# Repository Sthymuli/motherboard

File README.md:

\# Sthymuli-motherboard
This repo contains the PCB for the Sthymuli motherboard. Sthymuli is an educative robot aimed at children whith the aim of promoting collaborative learning.

The motherboard is designed arround a doughnut shape with addons that plug in the center. the shape was chosen to encourage equal access to up to four children at a time interracting with the device.

## 3D view

| Top | Bottom |
|---|---|
|  |  |

## Exports

Regenerated automatically by the [export workflow](.github/workflows/export.yml) on every push to `main` that changes the design:

* [Schematic (PDF)](exports/Sthymuli-motherboard_schematic.pdf)
* [Layout (PDF, one page per layer)](exports/Sthymuli-motherboard_layout.pdf)
* [3D model (STEP)](exports/Sthymuli-motherboard.step), with only the parts placed on the board
* [3D render, top](exports/Sthymuli-motherboard_3d_top.png) / [bottom](exports/Sthymuli-motherboard_3d_bottom.png)

To run the same export locally: `scripts/export.sh` (see the comment at the top of the script for the Flatpak KiCad variant).

The cardinal board can be found [here](https://github.com/Sthymuli/cardinalboard).

# Feature
The device contains the following sensors 

===

* # USB-C connector
* # Batterie + BMS
* # ESP32 + STM32
* # Speaker
* # Microphone
* # capacitive buttons (distributed arround the doughnut as discussed last time)
* # IR remote receive
* # 4 IR proximity Sensor
* # Motor Driver (so they can just connect the two wire of the motor and dont need to add a Hbridge on the dauther board
* # RGB LED (there I need to count how many and decide with you what we keep and what we breakout for the daugther board

\# Daugther boards

the following will be available for the daugther board :

* IMU
* color sensor
* 2 DC motor channel
* LEDs
* IR proximity sensor / analog pin that can be used for sensing

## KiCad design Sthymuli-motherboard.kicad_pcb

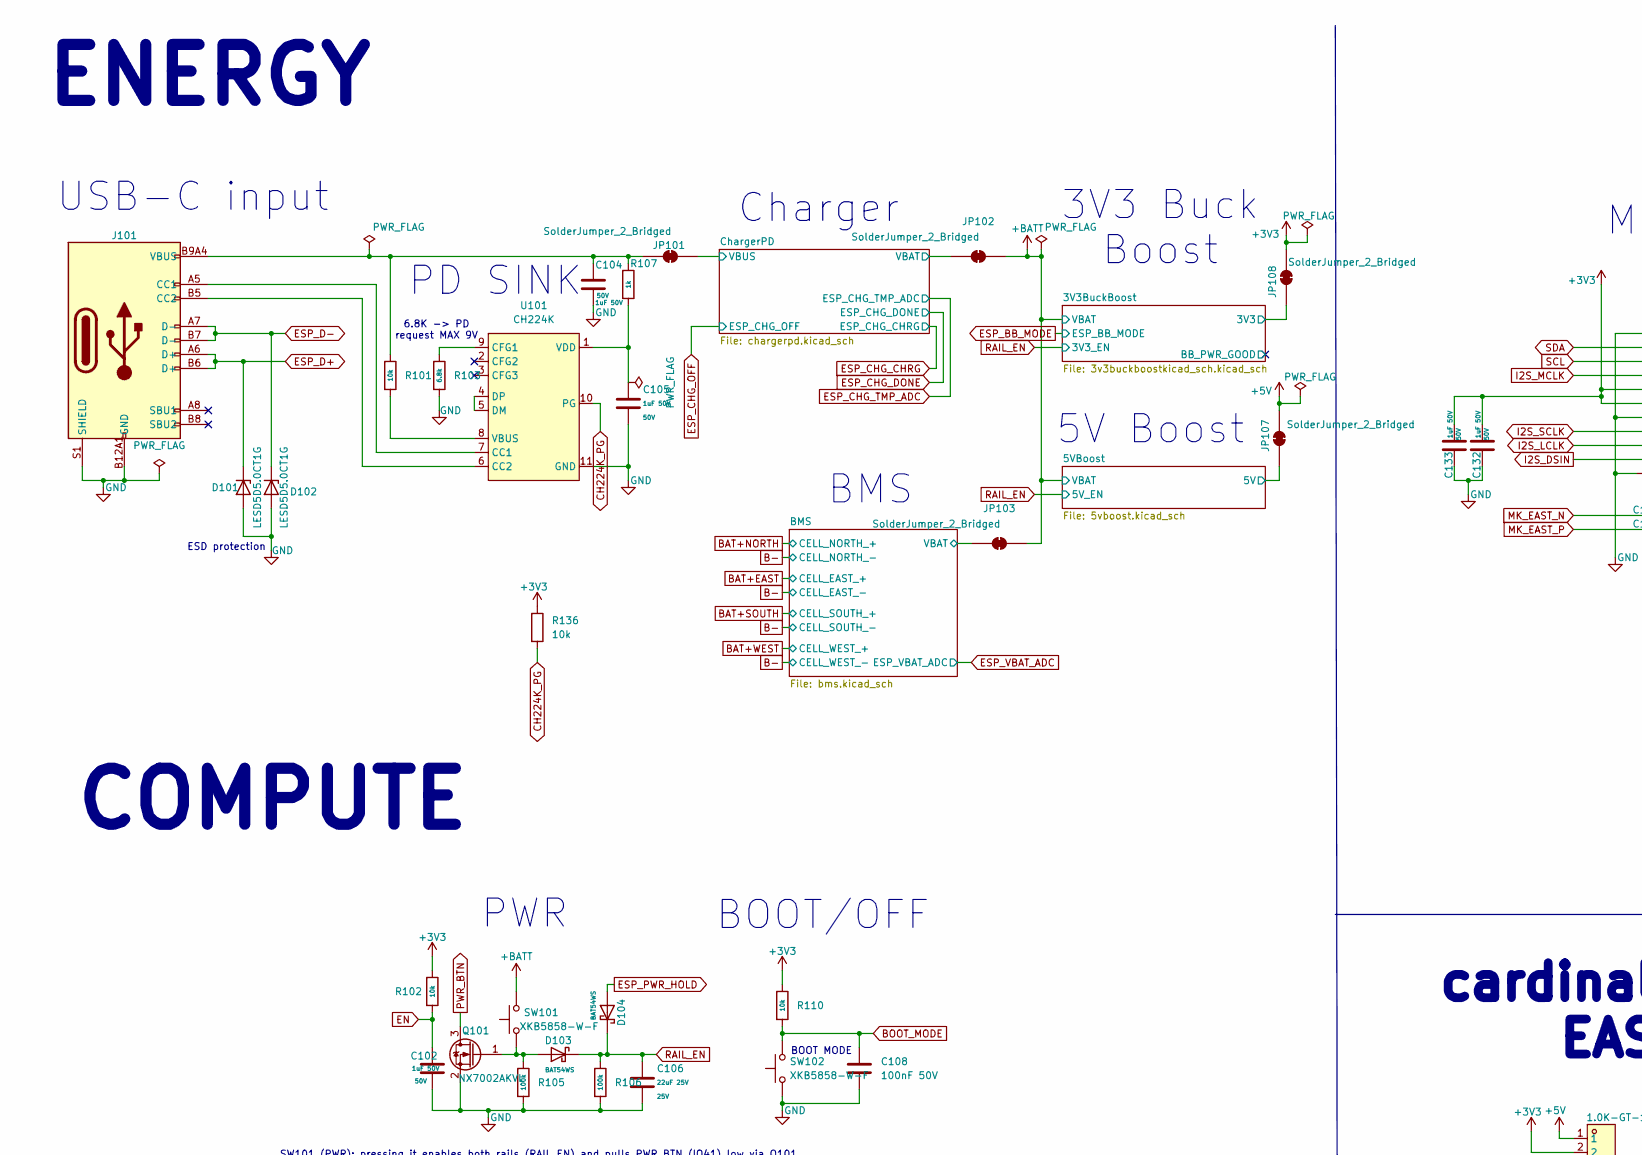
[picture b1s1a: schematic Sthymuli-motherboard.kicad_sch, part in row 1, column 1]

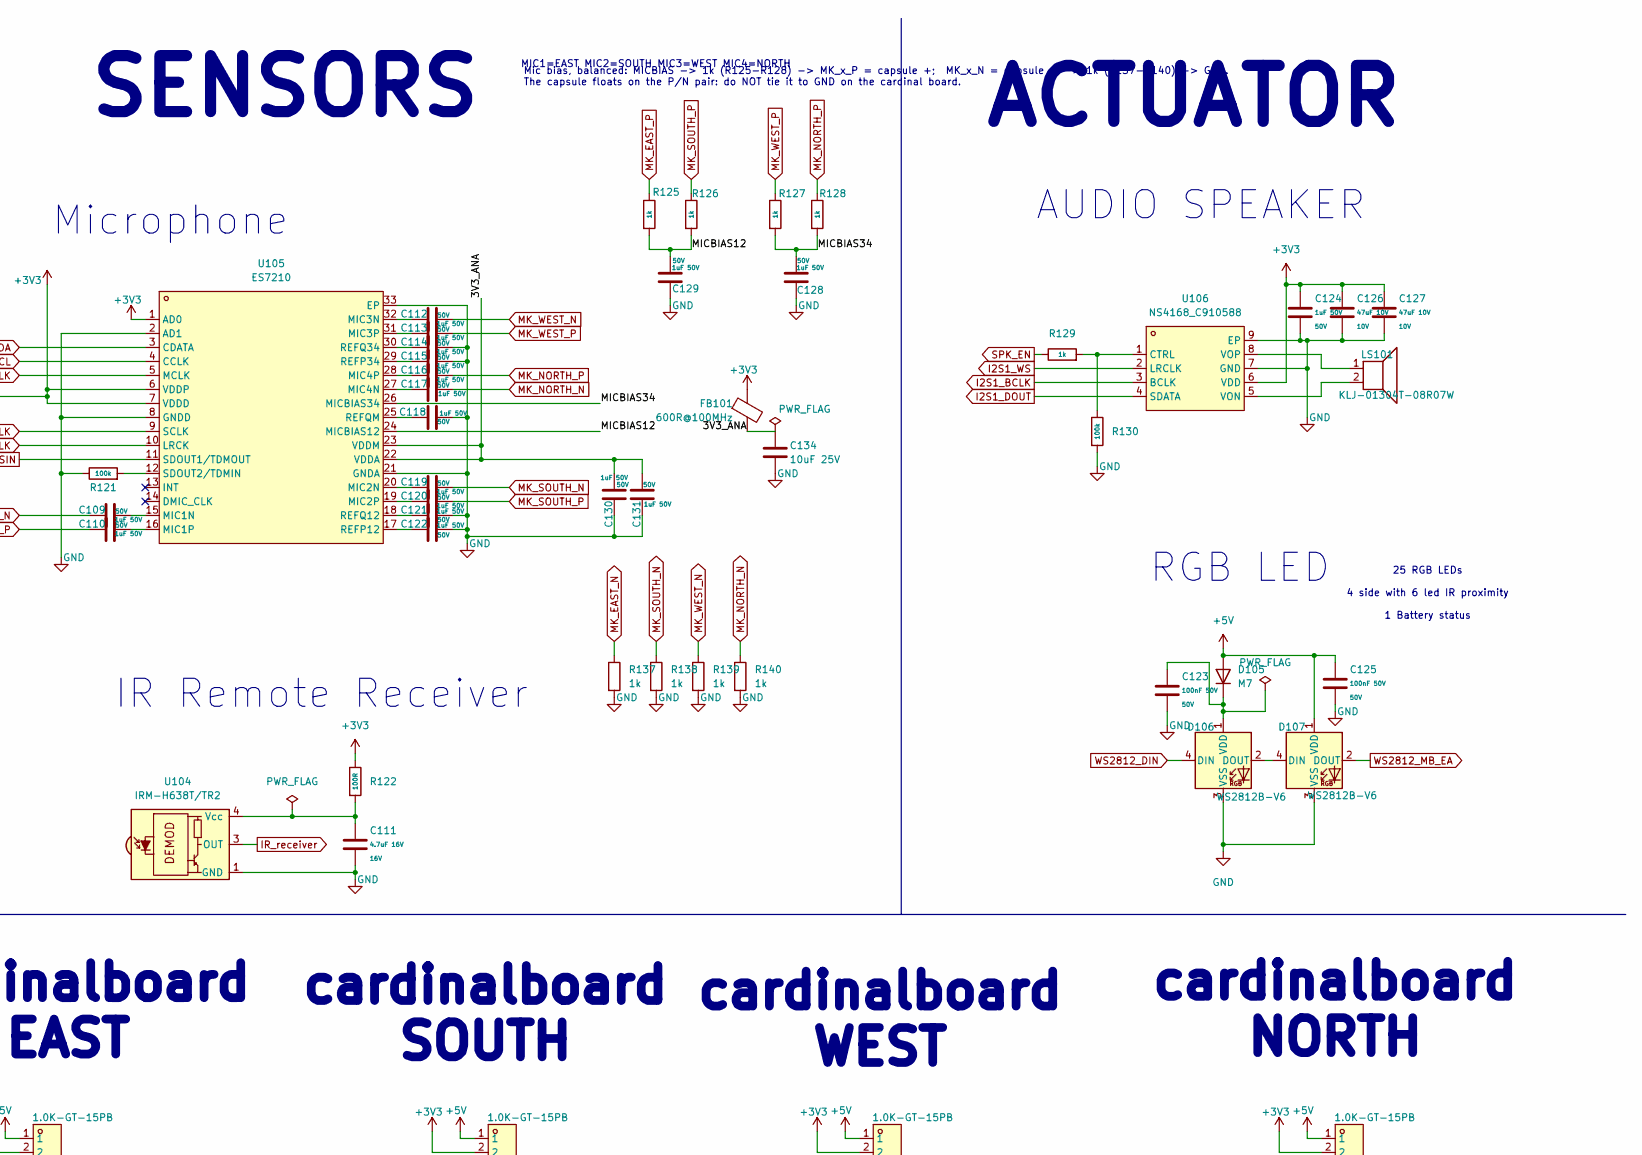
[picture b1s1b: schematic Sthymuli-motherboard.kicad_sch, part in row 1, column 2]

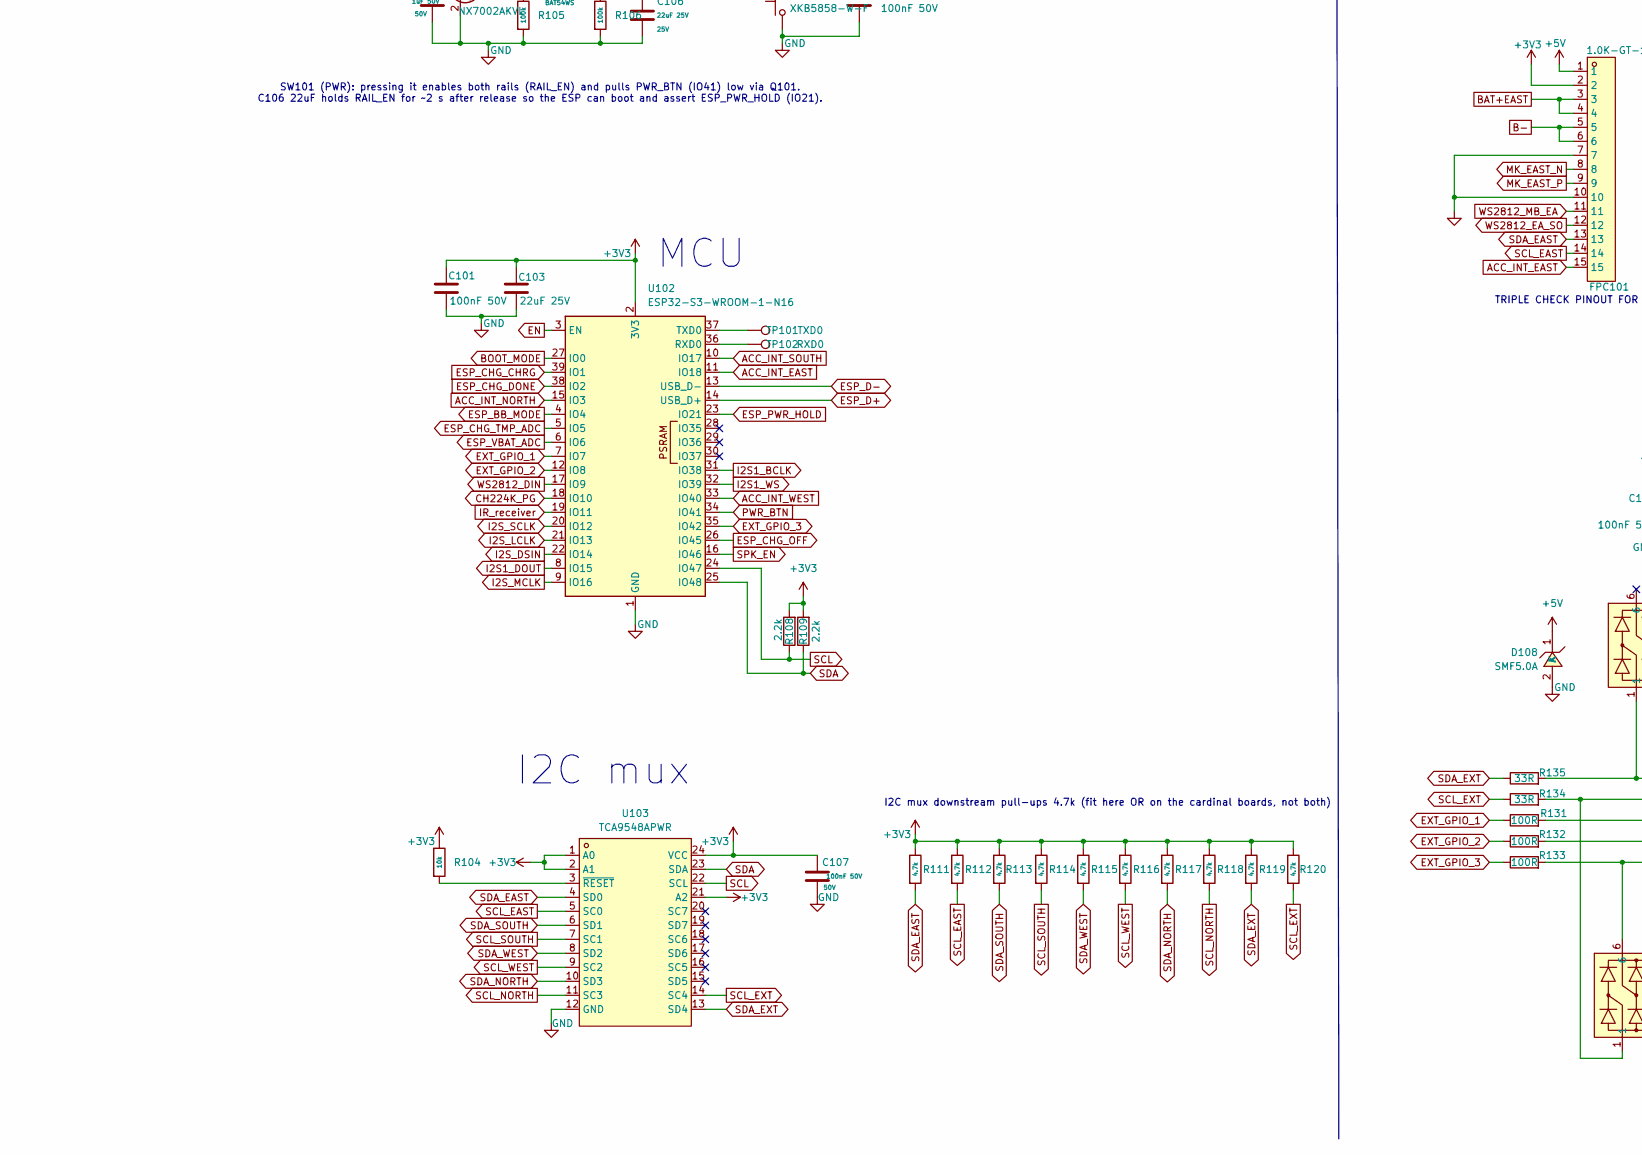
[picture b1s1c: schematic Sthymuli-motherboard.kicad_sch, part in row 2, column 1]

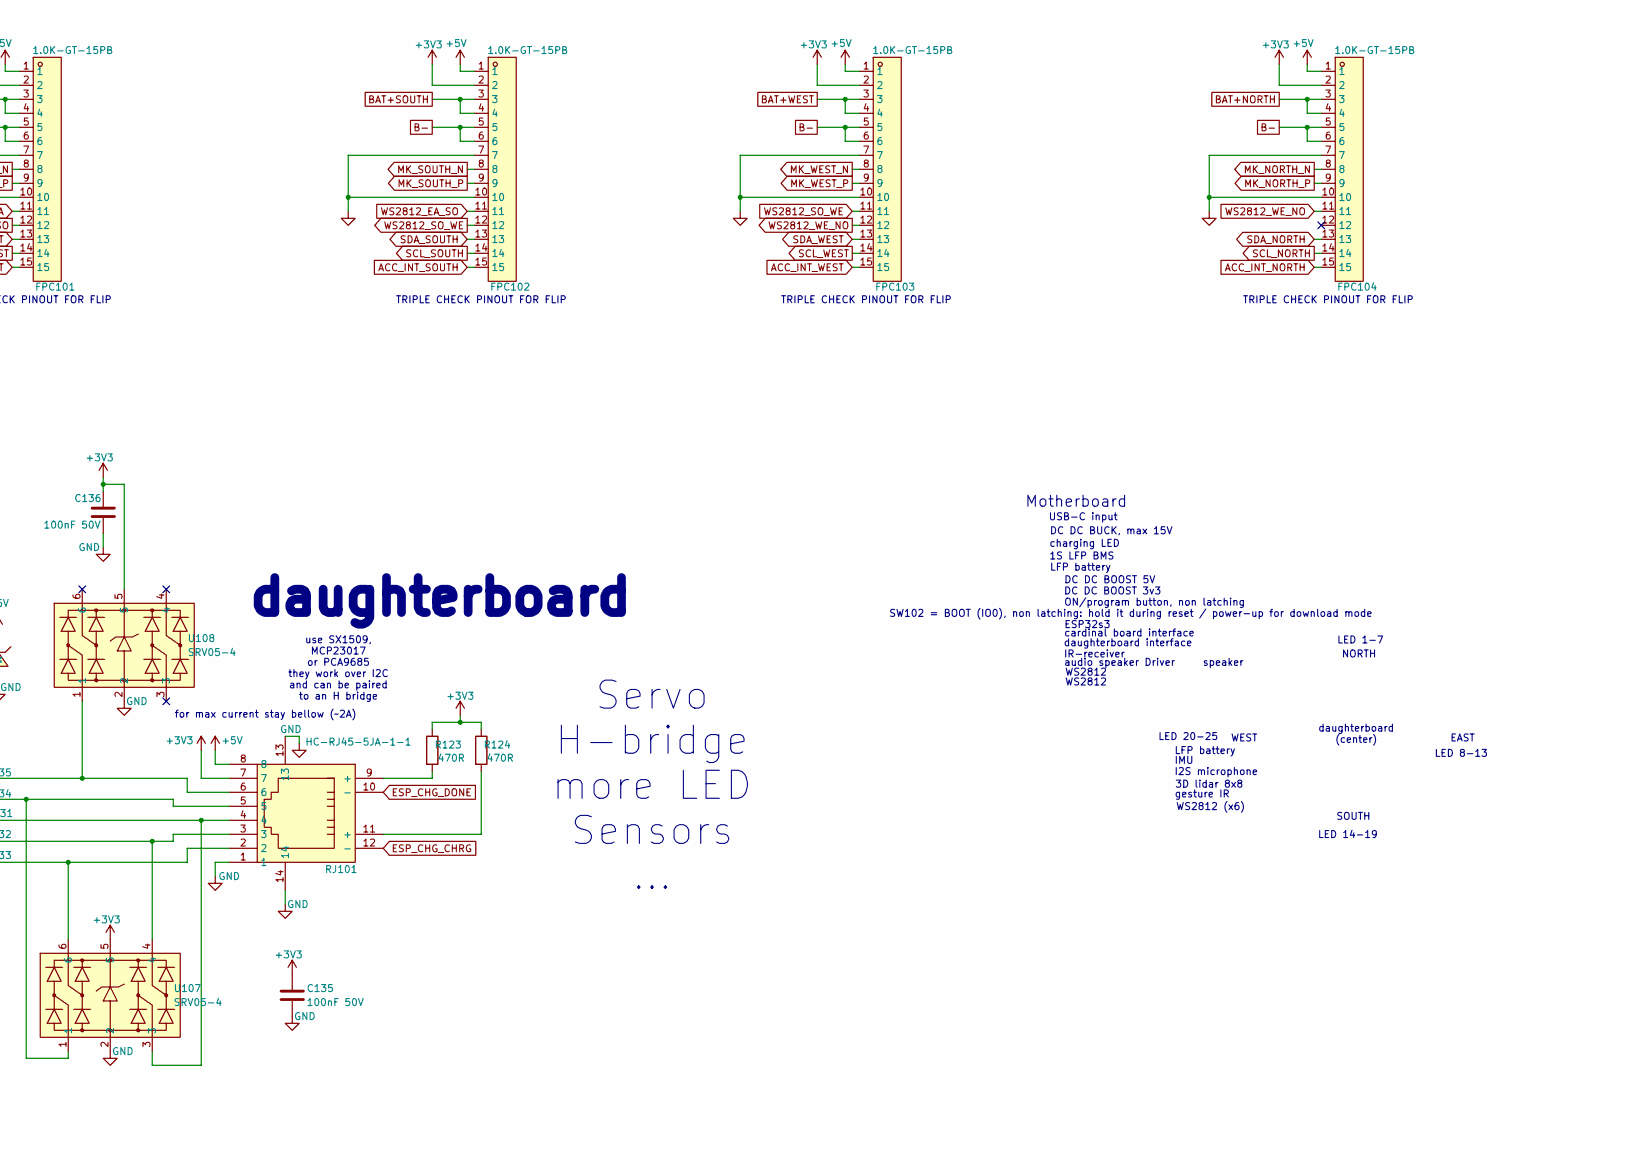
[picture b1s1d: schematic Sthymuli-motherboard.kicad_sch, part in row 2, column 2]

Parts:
C101, C108, C135, C136: 100nF 50V; C_0603_1608Metric; LCSC C14663
C102, C104, C105, C109, C110, C112, C113, C114, C115, C116, C117, C118, C119, C120, C121, C122, C124, C128, C129, C130, C131, C132, C133: 1uF 50V; C_0603_1608Metric; Voltage Rated 50V; Tolerance ±10%; Part CL10A105KB8NNNC; LCSC C15849
C103: 22uF 25V; C_0805_2012Metric; LCSC C45783
C106: 22uF 25V; C_0805_2012Metric; Voltage Rated 25V; Tolerance ±20%; Part CL21A226MAQNNNE; LCSC C45783
C107, C123, C125: 100nF 50V; C_0603_1608Metric; Voltage Rated 50V; Tolerance ±10%; Part CC0603KRX7R9BB104; LCSC C14663
C111: 4.7uF 16V; C_0603_1608Metric; Voltage Rated 16V; Tolerance ±10%; Part CL10A475KO8NNNC; LCSC C19666
C126, C127: 47uF 10V; C_1206_3216Metric; Voltage Rated 10V; Tolerance ±20%; Part CL31A476MPHNNNE; LCSC C96123
C134: 10uF 25V; C_0805_2012Metric; LCSC C15850
D101, D102: LESD5D5.0CT1G; D_SOD-523; LCSC C5246195
D103, D104: BAT54WS; D_SOD-323; Forward Voltage (Vf@If) 1V@100mA; Reverse Voltage (Vr) 30V; Part BAT54WS; LCSC C7502694
D105: M7; D_SMA; LCSC C95872
D106, D107: WS2812B-V6; LED_WS2812B_PLCC4_5.0x5.0mm_P3.2mm; LCSC C52917433
D108: SMF5.0A; SOD-123F_L2.8-W1.8-LS3.7-RD; LCSC C151296
FB101: 600R@100MHz; L_0805_2012Metric; LCSC C1017
FPC101, FPC102, FPC103, FPC104: 1.0K-GT-15PB; FPC-SMD_15P-P1.00_HDGC_1.0K-GT-15PB; MPN 1.0K-GT-15PB; LCSC Part C2915527
J101: HC-TYPE-C-16P-FL6.65Q-5A-06; CONN-TH_HC-TYPE-C-16P-FL6.65Q-5A-06; LCSC C5342434
JP101, JP102, JP103, JP107, JP108: SolderJumper_2_Bridged; SolderJumper-2_P1.3mm_Bridged_Pad1.0x1.5mm
LS101: KLJ-01304T-08R07W; Speaker KELIKING KLJ-01304T-08R07W; LCSC C18186315
Q101: NX7002AKVL; SOT-23; LCSC C551606
R101, R102, R104, R110: 10k; R_0603_1608Metric; Overload Voltage (Max) 75V; Tolerance ±1%; Part 0603WAF1002T5E; LCSC C25804
R103: 6.8k; R_0603_1608Metric; Overload Voltage (Max) 75V; Tolerance ±1%; Part 0603WAF6801T5E; LCSC C23212
R105, R106, R121, R130: 100k; R_0603_1608Metric; Overload Voltage (Max) 75V; Tolerance ±1%; Part 0603WAF1003T5E; LCSC C25803
R107: 1k; R_1206_3216Metric; Overload Voltage (Max) 200V; Tolerance ±1%; Part 1206W4F1001T5E; LCSC C4410
R108, R109: 2.2k; R_0603_1608Metric; LCSC C4190
R111, R112, R113, R114, R115, R116, R117, R118, R119, R120: 4.7k; R_0603_1608Metric; Overload Voltage (Max) 75V; Tolerance ±1%; Part 0603WAF4701T5E; LCSC C23162
R122: 100R; R_0603_1608Metric; Overload Voltage (Max) 75V; Tolerance ±1%; Part 0603WAF1000T5E; LCSC C22775
R123, R124: 470R; R_0603_1608Metric; LCSC C23179
R125, R126, R127, R128, R129: 1k; R_0603_1608Metric; Overload Voltage (Max) 75V; Tolerance ±1%; Part 0603WAF1001T5E; LCSC C21190
R131, R132, R133: 100R; R_0603_1608Metric; LCSC C22775
R134, R135: 33R; R_0603_1608Metric; LCSC C23140
R136: 10k; R_0603_1608Metric; LCSC C25804
R137, R138, R139, R140: 1k; R_0603_1608Metric; LCSC C21190
RJ101: HC-RJ45-5JA-1-1; RJ45-TH_HC-RJ45-5JA-1-1; MPN HC-RJ45-5JA-1-1; LCSC Part C3000171
SW101, SW102: XKB5858-W-F; XKB5858; LCSC C2884737
TP101: TXD0; TestPoint_Pad_D1.0mm
TP102: RXD0; TestPoint_Pad_D1.0mm
U101: CH224K; ESSOP-10_L4.9-W3.9-P1.0-LS6.0-TL-EP; MPN CH224K; LCSC Part C970725
U102: ESP32-S3-WROOM-1-N16; ESP32-S3-WROOM-1; LCSC C2913199
U103: TCA9548APWR; TSSOP-24_L7.8-W4.4-P0.65-LS6.4-BL; MPN TCA9548APWR; LCSC Part C130026
U104: IRM-H638T/TR2; Everlight_IRM-H6xxT; LCSC C91447
U105: ES7210; QFN-32_L4.0-W4.0-P0.40-BL-EP2.7; MPN ES7210; LCSC Part C365743
U106: NS4168_C910588; ESOP-8_L4.9-W3.9-P1.27-LS6.0-BL-EP; MPN NS4168; LCSC Part C910588
U107, U108: SRV05-4; SOT-23-6_L2.9-W1.6-P0.95-LS2.8-BL; LCSC C558418

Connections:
+3V3: C101.1, C103.1, C107.1, C124.1, C126.1, C127.1, C132.2, C133.2, C135.1, C136.1, FB101.1, FPC101.2, FPC102.2, FPC103.2, FPC104.2, JP108.1 (A), R102.1, R104.1, R108.2, R109.2, R110.1, R111.1, R112.1, R113.1, R114.1, R115.1, R116.1, R117.1, R118.1, R119.1, R120.1, R122.1, R123.1, R124.1, R136.1, RJ101.7, U102.2 (3V3), U103.1 (A0), U103.2 (A1), U103.21 (A2), U103.24 (VCC), U105.1 (AD0), U105.6 (VDDP), U105.7 (VDDD), U106.6 (VDD), U107.5, U108.5; also elsewhere on the board
+5V: C125.1, D105.2 (A), D107.1 (VDD), D108.1 (K), FPC101.1, FPC102.1, FPC103.1, FPC104.1, JP107.1 (A), RJ101.8
+BATT: JP102.2 (B), JP103.2 (B), SW101.2; also elsewhere on the board
/3V3BuckBoost/3V3: JP108.2 (B); also elsewhere on the board
/3V3_ANA: C130.2, C131.2, C134.1, FB101.2, U105.22 (VDDA), U105.23 (VDDM)
/5VBoost/5V: JP107.2 (B); also elsewhere on the board
/BMS/VBAT: JP103.1 (A); also elsewhere on the board
/ChargerPD/VBAT: JP102.1 (A); also elsewhere on the board
/ChargerPD/VBUS: JP101.2 (B); also elsewhere on the board
/MICBIAS12: C129.2, R125.2, R126.2, U105.24 (MICBIAS12)
/MICBIAS34: C128.2, R127.2, R128.2, U105.26 (MICBIAS34)
ACC_INT_EAST: FPC101.15, U102.11 (IO18)
ACC_INT_NORTH: FPC104.15, U102.15 (IO3)
ACC_INT_SOUTH: FPC102.15, U102.10 (IO17)
ACC_INT_WEST: FPC103.15, U102.33 (IO40)
B-: FPC101.5, FPC101.6, FPC102.5, FPC102.6, FPC103.5, FPC103.6, FPC104.5, FPC104.6; also elsewhere on the board
BAT+EAST: FPC101.3, FPC101.4; also elsewhere on the board
BAT+NORTH: FPC104.3, FPC104.4; also elsewhere on the board
BAT+SOUTH: FPC102.3, FPC102.4; also elsewhere on the board
BAT+WEST: FPC103.3, FPC103.4; also elsewhere on the board
BOOT_MODE: C108.1, R110.2, SW102.2, U102.27 (IO0)
CH224K_PG: R136.2, U101.10 (PG), U102.18 (IO10)
EN: C102.1, R102.2, U102.3 (EN)
ESP_BB_MODE: U102.4 (IO4); also elsewhere on the board
ESP_CHG_CHRG: RJ101.12 (-), U102.39 (IO1); also elsewhere on the board
ESP_CHG_DONE: RJ101.10 (-), U102.38 (IO2); also elsewhere on the board
ESP_CHG_OFF: U102.26 (IO45); also elsewhere on the board
ESP_CHG_TMP_ADC: U102.5 (IO5); also elsewhere on the board
ESP_D+: D101.1 (K), J101.A6 (D+), J101.B6 (D+), U102.14 (USB_D+)
ESP_D-: D102.1 (K), J101.A7 (D-), J101.B7 (D-), U102.13 (USB_D-)
ESP_PWR_HOLD: D104.2, U102.23 (IO21)
ESP_VBAT_ADC: U102.6 (IO6); also elsewhere on the board
EXT_GPIO_1: R131.1, U102.7 (IO7)
EXT_GPIO_2: R132.1, U102.12 (IO8)
EXT_GPIO_3: R133.1, U102.35 (IO42)
GND: C101.2, C102.2, C103.2, C104.2, C105.2, C106.2, C107.2, C108.2, C111.2, C114.2, C115.2, C118.2, C121.2, C122.2, C123.2, C124.2, C125.2, C126.2, C127.2, C128.1, C129.1, C130.1, C131.1, C132.1, C133.1, C134.2, C135.2, C136.2, D101.2 (A), D102.2 (A), D106.3 (VSS), D107.3 (VSS), D108.2 (A), FPC101.7, FPC101.10, FPC102.7, FPC102.10, FPC103.7, FPC103.10, FPC104.7, FPC104.10, J101.A12B1 (GND), J101.B12A1 (GND), J101.S1 (SHIELD), Q101.2 (S), R103.2, R105.2, R106.2, R121.1, R130.2, R137.2, R138.2, R139.2, R140.2, RJ101.1, RJ101.13, RJ101.14, SW102.1, U101.11 (GND), U102.1 (GND), U102.40 (GND), U102.41 (GND), U103.12 (GND), U104.1 (GND), U104.2 (GND), U105.2 (AD1), U105.8 (GNDD), U105.21 (GNDA), U105.33 (EP), U106.7 (GND), U106.9 (EP), U107.2, U108.2; also elsewhere on the board
I2S1_BCLK: U102.31 (IO38), U106.3 (BCLK)
I2S1_DOUT: U102.8 (IO15), U106.4 (SDATA)
I2S1_WS: U102.32 (IO39), U106.2 (LRCLK)
I2S_DSIN: U102.22 (IO14), U105.11 (SDOUT1/TDMOUT)
I2S_LCLK: U102.21 (IO13), U105.10 (LRCK)
I2S_MCLK: U102.9 (IO16), U105.5 (MCLK)
I2S_SCLK: U102.20 (IO12), U105.9 (SCLK)
IR_receiver: U102.19 (IO11), U104.3 (OUT)
MK_EAST_N: C109.1, FPC101.8, R137.1
MK_EAST_P: C110.1, FPC101.9, R125.1
MK_NORTH_N: C117.2, FPC104.8, R140.1
MK_NORTH_P: C116.2, FPC104.9, R128.1
MK_SOUTH_N: C119.2, FPC102.8, R138.1
MK_SOUTH_P: C120.2, FPC102.9, R126.1
MK_WEST_N: C112.2, FPC103.8, R139.1
MK_WEST_P: C113.2, FPC103.9, R127.1
unnamed: C123.1, D105.1 (K), D106.1 (VDD)
unnamed: D106.2 (DOUT), D107.4 (DIN)
unnamed: J101.A5 (CC1), U101.7 (CC1)
unnamed: J101.B5 (CC2), U101.6 (CC2)
unnamed: C104.1, J101.A9B4 (VBUS), J101.B9A4 (VBUS), JP101.1 (A), R101.1, R107.1
unnamed: D103.2, Q101.1 (G), R105.1, SW101.1
unnamed: R123.2, RJ101.9 (+)
unnamed: R124.2, RJ101.11 (+)
unnamed: R131.2, RJ101.4, U107.3
unnamed: R132.2, RJ101.3, U107.4
unnamed: R133.2, RJ101.2, U107.6
unnamed: R134.2, RJ101.5, U107.1
unnamed: R135.2, RJ101.6, U108.1
unnamed: R103.1, U101.9 (CFG1)
unnamed: U101.4 (DP), U101.5 (DM)
unnamed: R101.2, U101.8 (VBUS)
unnamed: C105.1, R107.2, U101.1 (VDD)
unnamed: TP102.1 (1_1), U102.36 (RXD0)
unnamed: TP101.1 (1_1), U102.37 (TXD0)
unnamed: R104.2, U103.3 (~RESET)
unnamed: C111.1, R122.2, U104.4 (Vcc)
unnamed: C109.2, U105.15 (MIC1N)
unnamed: C110.2, U105.16 (MIC1P)
unnamed: C119.1, U105.20 (MIC2N)
unnamed: C120.1, U105.19 (MIC2P)
unnamed: C112.1, U105.32 (MIC3N)
unnamed: C113.1, U105.31 (MIC3P)
unnamed: C117.1, U105.27 (MIC4N)
unnamed: C116.1, U105.28 (MIC4P)
unnamed: C122.1, U105.17 (REFP12)
unnamed: C115.1, U105.29 (REFP34)
unnamed: C121.1, U105.18 (REFQ12)
unnamed: C114.1, U105.30 (REFQ34)
unnamed: C118.1, U105.25 (REFQM)
unnamed: R121.2, U105.12 (SDOUT2/TDMIN)
unnamed: R129.2, R130.1, U106.1 (CTRL)
unnamed: LS101.2, U106.5 (VON)
unnamed: LS101.1, U106.8 (VOP)
PWR_BTN: Q101.3 (D), U102.34 (IO41)
RAIL_EN: C106.1, D103.1, D104.1, R106.1; also elsewhere on the board
SCL: R108.1, U102.24 (IO47), U103.22 (SCL), U105.4 (CCLK)
SCL_EAST: FPC101.14, R112.2, U103.5 (SC0)
SCL_EXT: R120.2, R134.1, U103.14 (SC4)
SCL_NORTH: FPC104.14, R118.2, U103.11 (SC3)
SCL_SOUTH: FPC102.14, R114.2, U103.7 (SC1)
SCL_WEST: FPC103.14, R116.2, U103.9 (SC2)
SDA: R109.1, U102.25 (IO48), U103.23 (SDA), U105.3 (CDATA)
SDA_EAST: FPC101.13, R111.2, U103.4 (SD0)
SDA_EXT: R119.2, R135.1, U103.13 (SD4)
SDA_NORTH: FPC104.13, R117.2, U103.10 (SD3)
SDA_SOUTH: FPC102.13, R113.2, U103.6 (SD1)
SDA_WEST: FPC103.13, R115.2, U103.8 (SD2)
SPK_EN: R129.1, U102.16 (IO46)
WS2812_DIN: D106.4 (DIN), U102.17 (IO9)
WS2812_EA_SO: FPC101.12, FPC102.11
WS2812_MB_EA: D107.2 (DOUT), FPC101.11
WS2812_SO_WE: FPC102.12, FPC103.11
WS2812_WE_NO: FPC103.12, FPC104.11

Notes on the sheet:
SOUTH
cardinalboard NORTH
MIC1=EAST MIC2=SOUTH MIC3=WEST MIC4=NORTH
Servo H-bridge more LED Sensors ...
USB-C input
DC DC BUCK, max 15V
25 RGB LEDs 4 side with 6 led IR proximity 1 Battery status
LFP battery
BOOT/OFF
Mic bias, balanced: MICBIAS -> 1k (R125-R128) -> MK_x_P = capsule +; MK_x_N = capsule - -> 1k (R137-R140) -> GND. The capsule floats on the P/N pair: do NOT tie it to GND on the cardinal board.
use SX1509, MCP23017 or PCA9685 they work over I2C and can be paired to an H bridge
SW101 (PWR): pressing it enables both rails (RAIL_EN) and pulls PWR_BTN (IO41) low via Q101. C106 22uF holds RAIL_EN for ~2 s after release so the ESP can boot and assert ESP_PWR_HOLD (IO21).
ACTUATOR
DC DC BOOST 5V
AUDIO SPEAKER
LED 8-13
5V Boost
MCU
TRIPLE CHECK PINOUT FOR FLIP
WS2812
EAST
3D lidar 8x8
I2C mux
IR Remote Receiver
cardinal board interface
audio speaker Driver
cardinalboard SOUTH
Microphone
daughterboard (center)
PD SINK
BMS
cardinalboard EAST
WS2812 (x6)
Charger
IMU
speaker
I2S microphone
COMPUTE
ENERGY
gesture IR

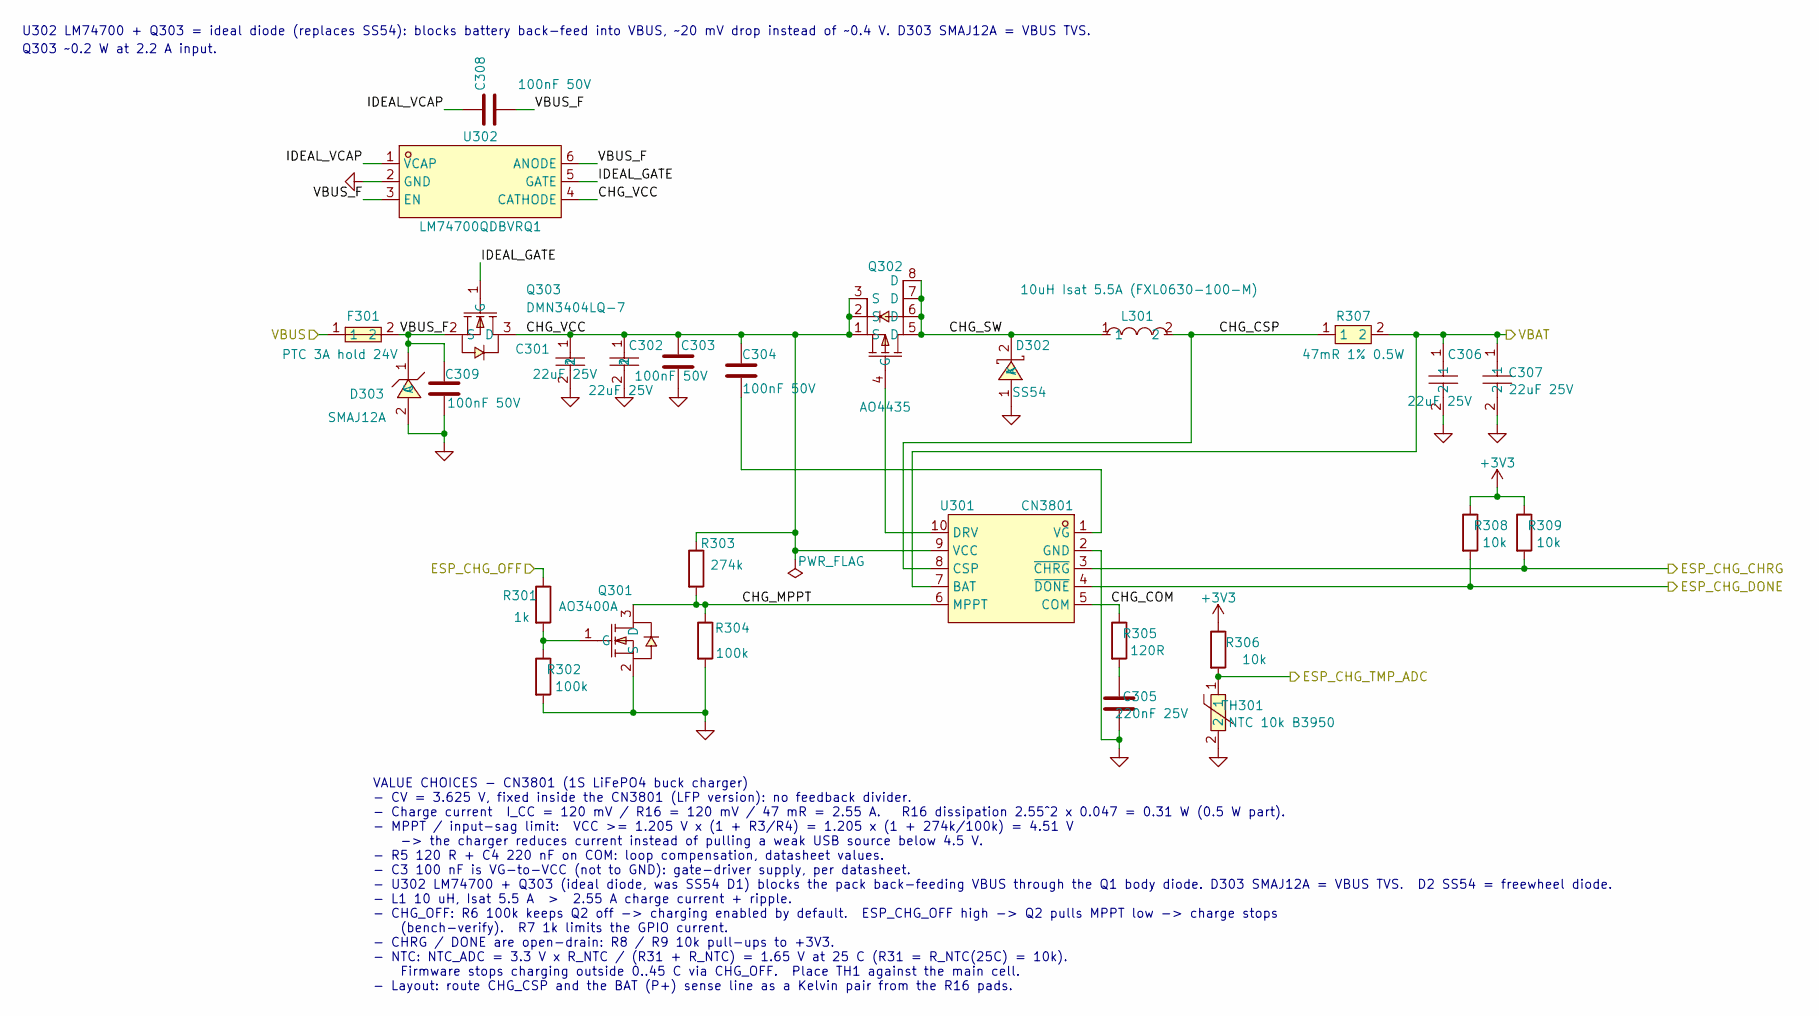
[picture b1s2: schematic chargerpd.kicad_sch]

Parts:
C301, C302: 22uF 25V; C_1206_3216Metric; MPN CL31A226KAHNNNE; LCSC C12891
C303, C304, C308, C309: 100nF 50V; C_0603_1608Metric; LCSC C14663
C305: 220nF 25V; C_0603_1608Metric; LCSC C21120
C306, C307: 22uF 25V; C_0805_2012Metric; LCSC C45783
D302: SS54; SMA_L4.4-W2.8-LS5.4-R-RD; LCSC C22452
D303: SMAJ12A; SMA_L4.3-W2.6-LS5.2-RD; LCSC C148213
F301: PTC 3A hold 24V; F1812; LCSC C2892380
L301: 10uH Isat 5.5A (FXL0630-100-M); IND-SMD_L7.3-W6.8; LCSC C167223
Q301: AO3400A; SOT-23-3_L2.9-W1.3-P1.90-LS2.4-BR; LCSC C20917
Q302: AO4435; SOIC-8_L4.9-W3.8-P1.27-LS6.0-BL; LCSC C5224296
Q303: DMN3404LQ-7; SOT-23-3_L2.9-W1.3-P1.90-LS2.4; LCSC C461021
R301: 1k; R_0603_1608Metric; LCSC C21190
R302, R304: 100k; R_0603_1608Metric; LCSC C25803
R303: 274k; R_0603_1608Metric; LCSC C22968
R305: 120R; R_0603_1608Metric; LCSC C22787
R306, R308, R309: 10k; R_0603_1608Metric; LCSC C25804
R307: 47mR 1% 0.5W; RES-SMD_L3.2-W1.6; LCSC C859912
TH301: NTC 10k B3950; R_0603_1608Metric; LCSC C2889049
U301: CN3801; SSOP-10_L4.9-W3.9-P1.00-LS6.0-BL; LCSC C840499
U302: LM74700QDBVRQ1; SOT-23-6_L2.9-W1.6-P0.95-LS2.8-BL; LCSC C2941042

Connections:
+3V3: R306.1, R308.1, R309.1; also elsewhere on the board
/ChargerPD/CHG_COM: R305.1, U301.5 (COM)
/ChargerPD/CHG_CSP: L301.2, R307.1, U301.8 (CSP)
/ChargerPD/CHG_MPPT: Q301.3 (D), R303.2, R304.1, U301.6 (MPPT)
/ChargerPD/CHG_SW: D302.2 (K), L301.1, Q302.5 (D), Q302.6 (D), Q302.7 (D), Q302.8 (D)
/ChargerPD/CHG_VCC: C301.1, C302.1, C303.1, C304.2, Q302.1 (S), Q302.2 (S), Q302.3 (S), Q303.3 (D), R303.1, U301.9 (VCC), U302.4 (CATHODE)
/ChargerPD/IDEAL_GATE: Q303.1 (G), U302.5 (GATE)
/ChargerPD/IDEAL_VCAP: C308.1, U302.1 (VCAP)
/ChargerPD/VBAT: C306.1, C307.1, R307.2, U301.7 (BAT); also elsewhere on the board
/ChargerPD/VBUS: F301.1; also elsewhere on the board
/ChargerPD/VBUS_F: C308.2, C309.1, D303.1 (C), F301.2, Q303.2 (S), U302.3 (EN), U302.6 (ANODE)
ESP_CHG_CHRG: R309.2, U301.3 (~CHRG); also elsewhere on the board
ESP_CHG_DONE: R308.2, U301.4 (~DONE); also elsewhere on the board
ESP_CHG_OFF: R301.1; also elsewhere on the board
ESP_CHG_TMP_ADC: R306.2, TH301.1; also elsewhere on the board
GND: C301.2, C302.2, C303.2, C305.2, C306.2, C307.2, C309.2, D302.1 (A), D303.2 (A), Q301.2 (S), R302.2, R304.2, TH301.2, U301.2 (GND), U302.2 (GND); also elsewhere on the board
unnamed: C305.1, R305.2
unnamed: Q301.1 (G), R301.2, R302.1
unnamed: Q302.4 (G), U301.10 (DRV)
unnamed: C304.1, U301.1 (VG)

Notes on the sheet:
VALUE CHOICES - CN3801 (1S LiFePO4 buck charger) - CV = 3.625 V, fixed inside the CN3801 (LFP version): no feedback divider. - Charge current I_CC = 120 mV / R16 = 120 mV / 47 mR = 2.55 A. R16 dissipation 2.55^2 x 0.047 = 0.31 W (0.5 W part). - MPPT / input-sag limit: VCC >= 1.205 V x (1 + R3/R4) =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
Q303 ~0.2 W at 2.2 A input.
U302 LM74700 + Q303 = ideal diode (replaces SS54): blocks battery back-feed into VBUS, ~20 mV drop instead of ~0.4 V. D303 SMAJ12A = VBUS TVS.

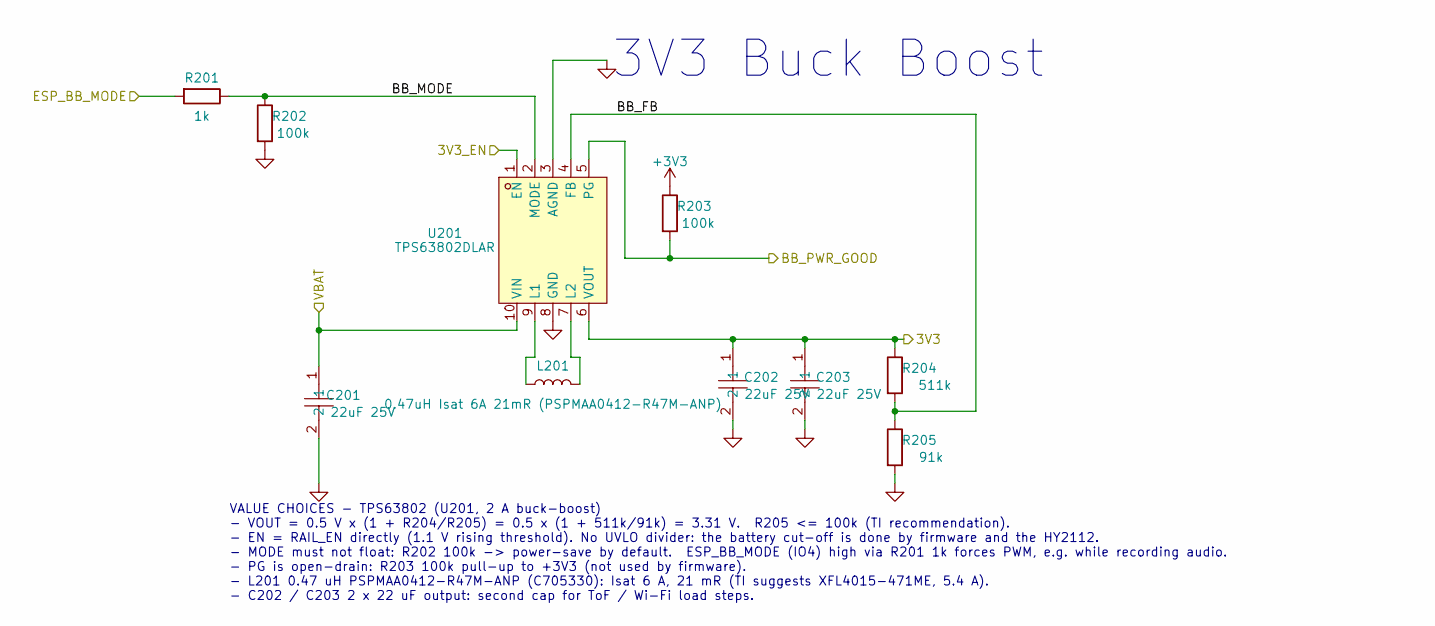
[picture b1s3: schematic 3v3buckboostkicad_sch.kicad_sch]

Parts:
C201, C202, C203: 22uF 25V; C_0805_2012Metric; LCSC C45783
L201: 0.47uH Isat 6A 21mR (PSPMAA0412-R47M-ANP); IND-SMD_L4.4-W4.2_PSPMAA0412; LCSC C705330
R201: 1k; R_0603_1608Metric; LCSC C21190
R202, R203: 100k; R_0603_1608Metric; LCSC C25803
R204: 511k; R_0603_1608Metric; LCSC C23194
R205: 91k; R_0603_1608Metric; LCSC C23265
U201: TPS63802DLAR; VSON-10_L3.0-W2.0-P0.50-TL; LCSC C2845237

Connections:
+3V3: R203.1; also elsewhere on the board
+BATT: C201.1, U201.10 (VIN); also elsewhere on the board
/3V3BuckBoost/3V3: C202.1, C203.1, R204.1, U201.6 (VOUT); also elsewhere on the board
/3V3BuckBoost/BB_FB: R204.2, R205.1, U201.4 (FB)
/3V3BuckBoost/BB_MODE: R201.1, R202.1, U201.2 (MODE)
/3V3BuckBoost/BB_PWR_GOOD: R203.2, U201.5 (PG)
ESP_BB_MODE: R201.2; also elsewhere on the board
GND: C201.2, C202.2, C203.2, R202.2, R205.2, U201.3 (AGND), U201.8 (GND); also elsewhere on the board
unnamed: L201.1, U201.9 (L1)
unnamed: L201.2, U201.7 (L2)
RAIL_EN: U201.1 (EN); also elsewhere on the board

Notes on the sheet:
VALUE CHOICES - TPS63802 (U201, 2 A buck-boost) - VOUT = 0.5 V x (1 + R204/R205) = 0.5 x (1 + 511k/91k) = 3.31 V. R205 <= 100k (TI recommendation). - EN = RAIL_EN directly (1.1 V rising threshold). No UVLO divider: the battery cut-off is done by firmware and the HY2112. - MODE must not float: R202 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
3V3 Buck Boost

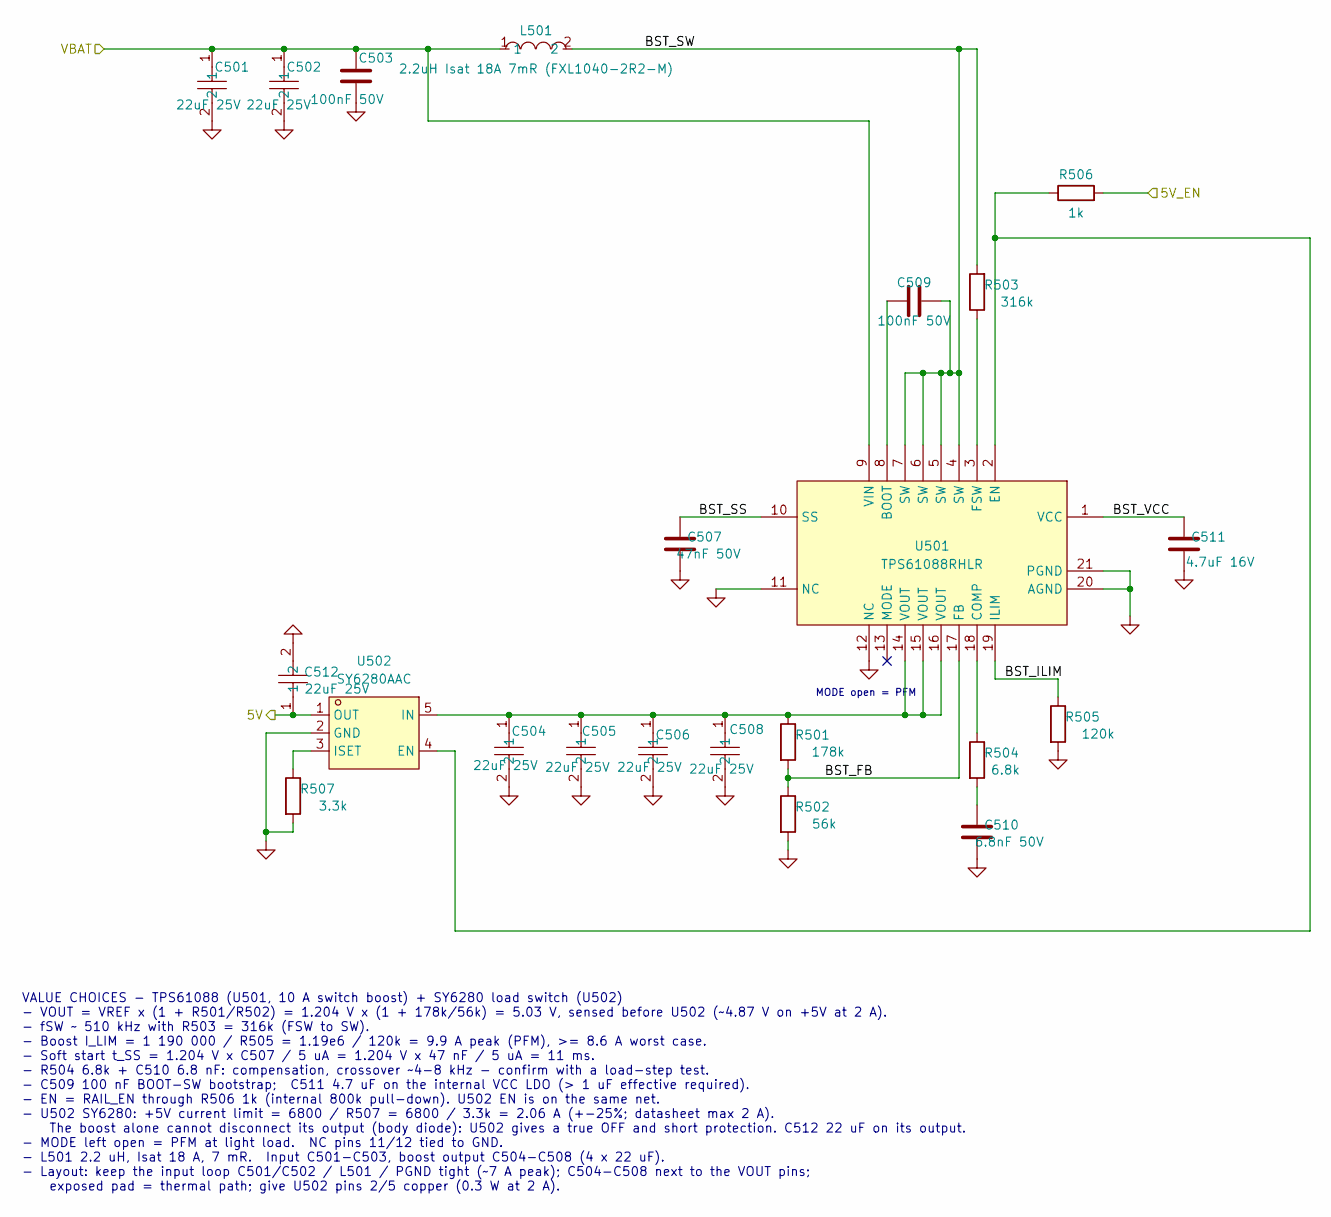
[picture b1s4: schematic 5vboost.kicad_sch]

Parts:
C501, C502, C504, C505, C506, C508, C512: 22uF 25V; C_0805_2012Metric; LCSC C45783
C503, C509: 100nF 50V; C_0603_1608Metric; LCSC C14663
C507: 47nF 50V; C_0603_1608Metric; LCSC C1622
C510: 6.8nF 50V; C_0603_1608Metric; LCSC C1631
C511: 4.7uF 16V; C_0603_1608Metric; LCSC C19666
L501: 2.2uH Isat 18A 7mR (FXL1040-2R2-M); IND-SMD_L11.5-W10.5; LCSC C167228
R501: 178k; R_0603_1608Metric; LCSC C22823
R502: 56k; R_0603_1608Metric; LCSC C23206
R503: 316k; R_0603_1608Metric; LCSC C25814
R504: 6.8k; R_0603_1608Metric; LCSC C23212
R505: 120k; R_0603_1608Metric; LCSC C25808
R506: 1k; R_0603_1608Metric; LCSC C21190
R507: 3.3k; R_0603_1608Metric; LCSC C22978
U501: TPS61088RHLR; VQFN-20_L4.6-W3.6-P0.50-BL; LCSC C87357
U502: SY6280AAC; SOT-23-5_L3.0-W1.7-P0.95-LS2.8-BL; MPN SY6280AAC; LCSC C55136

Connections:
+BATT: C501.1, C502.1, C503.1, L501.1, U501.9 (VIN); also elsewhere on the board
/5VBoost/5V: C512.1, U502.1 (OUT); also elsewhere on the board
/5VBoost/BST_FB: R501.2, R502.1, U501.17 (FB)
/5VBoost/BST_ILIM: R505.1, U501.19 (ILIM)
/5VBoost/BST_SS: C507.1, U501.10 (SS)
/5VBoost/BST_SW: C509.2, L501.2, R503.2, U501.4 (SW), U501.5 (SW), U501.6 (SW), U501.7 (SW)
/5VBoost/BST_VCC: C511.1, U501.1 (VCC)
GND: C501.2, C502.2, C503.2, C504.2, C505.2, C506.2, C507.2, C508.2, C510.2, C511.2, C512.2, R502.2, R505.2, R507.2, U501.11 (NC), U501.12 (NC), U501.20 (AGND), U501.21 (PGND), U502.2 (GND); also elsewhere on the board
unnamed: C510.1, R504.2
unnamed: C509.1, U501.8 (BOOT)
unnamed: R504.1, U501.18 (COMP)
unnamed: R506.1, U501.2 (EN), U502.4 (EN)
unnamed: R503.1, U501.3 (FSW)
unnamed: C504.1, C505.1, C506.1, C508.1, R501.1, U501.14 (VOUT), U501.15 (VOUT), U501.16 (VOUT), U502.5 (IN)
unnamed: R507.1, U502.3 (ISET)
RAIL_EN: R506.2; also elsewhere on the board

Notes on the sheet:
VALUE CHOICES - TPS61088 (U501, 10 A switch boost) + SY6280 load switch (U502) - VOUT = VREF x (1 + R501/R502) = 1.204 V x (1 + 178k/56k) = 5.03 V, sensed before U502 (~4.87 V on +5V at 2 A). - fSW ~ 510 kHz with R503 = 316k (FSW to SW). - Boost I_LIM = 1 190 000 / R505 = 1.19e6 / 120k = 9.9 A peak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
MODE open = PFM
